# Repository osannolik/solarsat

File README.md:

# Satellite model

- Solar cell charging of LiPo using SPV1050
- Sensor board with environmental sensor BME680 reports temperature and battery voltage over Bluetooth using nRF52832

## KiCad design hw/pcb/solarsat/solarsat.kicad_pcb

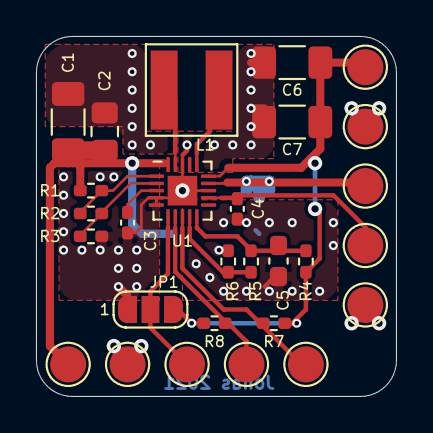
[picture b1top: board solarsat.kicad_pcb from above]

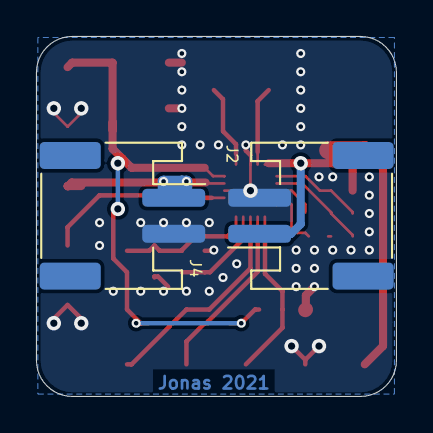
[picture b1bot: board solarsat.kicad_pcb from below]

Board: 2 copper layers, 20.0 x 20.0 mm, 30 parts (2 on the bottom side), 15 nets.

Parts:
C1: 4u7; C_1206_3216Metric_Pad1.33x1.80mm_HandSolder
C2: DNM; C_0805_2012Metric_Pad1.18x1.45mm_HandSolder
C3: 10n; C_0402_1005Metric_Pad0.74x0.62mm_HandSolder
C4: 100n; C_0402_1005Metric_Pad0.74x0.62mm_HandSolder
C5: 470n; C_0603_1608Metric_Pad1.08x0.95mm_HandSolder
C6, C7: 22u; C_1206_3216Metric_Pad1.33x1.80mm_HandSolder
J1, J3, J5, J6, J7, J8, J9, J10, J11, J12: Conn_01x01; TestPoint_Pad_D2.0mm
J2, J4: Conn_01x02; JST_PH_S2B-PH-SM4-TB_1x02-1MP_P2.00mm_Horizontal
JP1: SolderJumper_3_Open; SolderJumper-3_P1.3mm_Open_RoundedPad1.0x1.5mm_NumberLabels
L1: 22u; WE-LQS
R1, R4, R7, R8: 10M; R_0402_1005Metric_Pad0.72x0.64mm_HandSolder
R2: 0M59; R_0402_1005Metric_Pad0.72x0.64mm_HandSolder
R3: 2M49; R_0402_1005Metric_Pad0.72x0.64mm_HandSolder
R5: 1M2; R_0402_1005Metric_Pad0.72x0.64mm_HandSolder
R6: 4M7; R_0402_1005Metric_Pad0.72x0.64mm_HandSolder
U1: SPV1050; QFN-20-1EP_3x3mm_P0.4mm_EP1.65x1.65mm

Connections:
+BATT: J4.1, J5.1, U1.14
/LDO2_3V3: C4.1, J8.1, U1.12
/LDO2_EN: J9.1, JP1.2, U1.6
/STORE: C6.1, C7.1, J6.1, JP1.3, R4.1, R7.1, R8.1, U1.15
/~BAT_CHG: J11.1, R8.2, U1.7
/~BAT_CON: J10.1, R7.2, U1.8
GND: C1.2, C2.2, C3.2, C4.2, C5.2, C6.2, C7.2, J2.2, J3.1, J4.2, J7.1, J12.1, JP1.1, R3.2, R6.2, U1.4, U1.5, U1.13, U1.18, U1.21
unnamed: C3.1, U1.3
unnamed: C5.1, R4.2, R5.1, U1.10
unnamed: L1.1, U1.19
unnamed: L1.2, U1.16
unnamed: R1.2, R2.1, U1.1
unnamed: R2.2, R3.1, U1.2
unnamed: R5.2, R6.1, U1.9
VBUS: C1.1, C2.1, J1.1, J2.1, R1.1, U1.20

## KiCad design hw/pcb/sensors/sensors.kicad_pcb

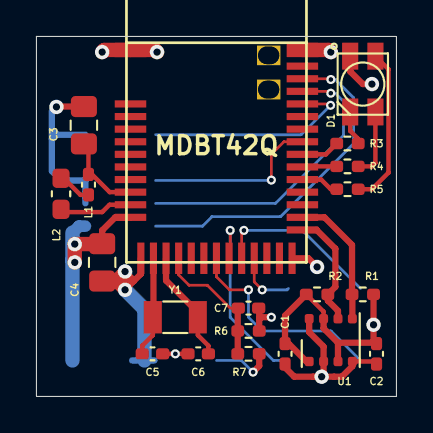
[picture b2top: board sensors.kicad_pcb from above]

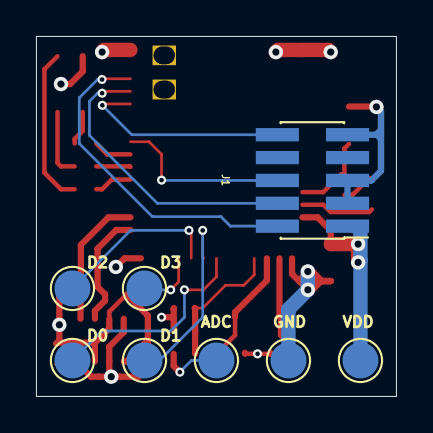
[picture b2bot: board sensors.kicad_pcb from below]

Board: 4 copper layers, 20.0 x 20.0 mm, 28 parts (8 on the bottom side), 25 nets.

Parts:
C1, C2: 100n; C_0402_1005Metric_Pad0.74x0.62mm_HandSolder
C3: 1 u; C_0805_2012Metric_Pad1.18x1.45mm_HandSolder
C4: 10 u; C_0805_2012Metric_Pad1.18x1.45mm_HandSolder
C5, C6: 12 p; C_0402_1005Metric_Pad0.74x0.62mm_HandSolder
C7: 10 n; C_0402_1005Metric_Pad0.74x0.62mm_HandSolder
D1: LED_ABRG; WL-SFTW
J1: Conn_ARM_JTAG_SWD_10; PinHeader_2x05_P1.27mm_Vertical_SMD
J2, J3, J4, J5, J6, J7, J8: Conn_01x01; TestPoint_Pad_D2.0mm
L1: 15 n; C_0402_1005Metric_Pad0.74x0.62mm_HandSolder
L2: 10 u; C_0603_1608Metric_Pad1.08x0.95mm_HandSolder
R1, R2: 4k7; R_0402_1005Metric_Pad0.72x0.64mm_HandSolder
R3, R4, R5, R6, R7: R; R_0402_1005Metric_Pad0.72x0.64mm_HandSolder
U1: BME680; Bosch_LGA-8_3x3mm_P0.8mm_ClockwisePinNumbering
U2: MDBT42Q
Y1: 32.768 kHz 9 pF FC-135; Crystal_SMD_3215-2Pin_3.2x1.5mm

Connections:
/ADC: C7.2, R6.2, R7.2, U2.15
/D0: J4.1, U2.18
/D1: J5.1, U2.19
/D2: J6.1, U2.20
/D3: J7.1, U2.21
/I2C_SCL: R1.1, U1.4, U2.26
/I2C_SDA: R2.1, U1.3, U2.25
/LED_B: R5.2, U2.29
/LED_G: R4.2, U2.30
/LED_R: R3.2, U2.31
/RESET: J1.10, U2.35
/SWDCLK: J1.4, U2.36
/SWDIO: J1.2, U2.37
/SWO: J1.6, U2.32
GND: C1.1, C2.1, C3.2, C4.2, C5.2, C6.2, C7.1, J1.3, J1.5, J1.9, J3.1, R6.1, U1.1, U1.5, U1.7, U2.1, U2.12, U2.24, U2.39
unnamed: C3.1, L1.1, U2.9
unnamed: C5.1, U2.13, Y1.1
unnamed: C6.1, U2.14, Y1.2
unnamed: D1.2, R5.1
unnamed: D1.3, R3.1
unnamed: D1.4, R4.1
unnamed: J8.1, R7.1
unnamed: L1.2, L2.1
unnamed: L2.2, U2.10
VDD: C1.2, C2.2, C4.1, D1.1, J1.1, J2.1, R1.2, R2.2, U1.2, U1.6, U1.8, U2.11

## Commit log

2021-07-23 separate power board with placements
2021-07-23 first routing
2021-07-25 routed
2021-07-25 thinner traces at spv package pins
2021-07-28 lipo battery under- and over voltage limits
2021-07-28 mppt configuration resistor values
2021-08-24 sensor board with nRF52
2021-09-15 add some component values
2021-10-16 silkscreen for r4 and r5 swapped...
2021-10-24 add pad to spv1050 symbol
2021-10-24 connect spv1050 pad to gnd
2021-10-27 rework layout: shield dcdc better
2021-10-27 add more shielding and another input cap, overkill is king
2021-10-27 increase size of store caps to 1206, and other smaller tweaks
2021-10-28 connect signal ground pin 4 directly to exposed pad gnd as per reference design
2021-10-29 removed ldo for 1.8 V
2021-10-30 minor pcb tweaks due to raging ocd
2023-01-26 initial sw based on nrf52 ble template
2023-01-26 remove unused experimental code
2023-01-26 first ble test - advertise dummy data
2023-01-28 send temperature and battery voltage in manufacturer data of ble advertise
2023-06-26 Update measurement and ble-advertisement intervals to update less often.
2023-07-08 pcb output
2023-07-08 readme and image
2023-07-08 Create LICENSE
